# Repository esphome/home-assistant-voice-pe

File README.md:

# Nanobot Voice PE firmware

This repository is a focused fork of the official ESPHome source code for the
[Home Assistant Voice: Preview Edition](https://www.home-assistant.io/voice-pe/).
The upstream project remains available at
[`esphome/home-assistant-voice-pe`](https://github.com/esphome/home-assistant-voice-pe).

> [!IMPORTANT]
> Das aktuelle gekoppelte Pre-Release ist Firmware [`v1.4.2`](https://github.com/aschauera/home-assistant-voice-pe/releases/tag/v1.4.2) zusammen mit HA Voice Bridge [`v1.4.2`](https://github.com/aschauera/NanoBotSkills/releases/tag/v1.4.2). Beide verwenden dieselbe SemVer und denselben `v`-Tag. Bis zur gemeinsamen Hardwarevalidierung bleiben beide Pre-Releases; historische Releases wie Firmware `0.2.1` und Bridge `v1.4.1` bleiben unverändert.

## Offener Dialogmodus

Die Custom Firmware unterstützt einen begrenzten halbduplexen Dialog über die
bestehende Home-Assistant-Assist-Pipeline. Ein Wake Word öffnet die Session;
nach jeder Antwort wartet das Gerät ohne neues Wake Word auf den nächsten Turn.
`Stop`, definierte Exit-Phrasen, Mute, die mittlere Taste, Fehler, zehn Minuten
Gesamtlaufzeit oder zwanzig Antworten beenden sie. Während auf eine Frage
gewartet wird, beenden zwanzig Sekunden ohne Sprachbeginn die Session. Der
Leerlauf-Timeout startet nach jeder Antwort neu und wird mit dem ersten
Sprachbeginn angehalten.

Der LED-Ablauf bleibt über Dialogzustände hinweg ruhig: ein kurzer grüner Ring
öffnet die Session; Warten und Zuhören teilen denselben violett atmenden Ring;
Verarbeitung und ein Remote-ACK bleiben langsam amberfarben; die Antwort nutzt
denselben Amber-Ton mit schnellerem Puls. Nach jeder Antwort wird wieder violett
gewartet. Ein normales Ende zeigt genau einen kurzen orangefarbenen Impuls,
Fehler blinken weiterhin rot. Der Diagnosesensor `Dialog state` behält die
genauen textuellen Zustände für Bridge-Diagnosen bei.

Eine eingebettete lokale Ansage „Einen Moment.“ kann über die ESPHome-Aktion
`dialog_remote_ack` ausgelöst werden. Die Conversation-Agent-Integration muss
diesen Hook erst nach erfolglosem Local-Intent-Routing aufrufen; die Firmware
selbst kann lokal und remote nicht unterscheiden.

Architektur, Zustandsübergänge, LED-Prioritäten, Integrationsvertrag, Grenzen
und Rollback sind in [`docs/dialogmodus.md`](docs/dialogmodus.md) dokumentiert.
Barge-in und Full-Duplex sind ausdrücklich nicht Bestandteil dieser Version.

## Nanobot LED override

The firmware exposes a **Nanobot LED state** select entity to Home Assistant.
Selecting a state temporarily overrides the stock Assist animation:

| Option | Visual feedback | Automatic reset |
|---|---|---|
| `off` | Return control to the stock firmware | immediate |
| `thinking` | slow amber breathing ring | 90 seconds |
| `ack` | same slow amber breathing ring; no separate blue indication | 1.5 seconds |
| `replying` | faster amber breathing ring | 90 seconds |
| `follow_up` | violet breathing ring | 90 seconds |
| `done` | green confirmation | 1 second |
| `error` | red flash | 3 seconds |

Startup failure, provisioning, loss of the Home Assistant connection, hardware
interaction, ringing timers, mute, and native Voice Assistant error/not-ready
states retain priority over the Nanobot override. Every long-lived override has
a 90-second fail-safe and boot always starts with the override disabled.

Home Assistant can drive the state with `select.select_option`, for example:

```yaml
action: select.select_option
target:
  entity_id: select.home_assistant_voice_0a6c07_nanobot_led_state
data:
  option: ack
```

The exact entity ID is assigned by Home Assistant and may differ.

## Building and installing

The GitHub Actions **Build** workflow validates both firmware variants with
ESPHome 2026.10.0 and publishes build artifacts. The custom firmware intentionally disables the
official HTTP updater so an upstream release cannot silently overwrite it;
future updates are installed through ESPHome OTA or USB.

Do not flash an untested artifact onto the only production Voice PE. Download
the workflow artifact and use `home-assistant-voice-esp32s3.factory.bin` for the
initial USB installation. Keep the official web installer as the rollback path:

https://esphome.github.io/home-assistant-voice-pe/

### Vorkompiliertes Release per OTA installieren

Die vollständige agentenlesbare Anleitung mit Download, Prüfsummenprüfung,
Erreichbarkeitstest, Upload, Verifikation und Rollback steht unter
[`docs/ota-flashing.md`](docs/ota-flashing.md). Die verbindliche Zuordnung von
Firmware- und Bridge-Releases steht unter
[`docs/release-pairing.md`](docs/release-pairing.md).

Kurzablauf für das Standard-Voice-PE; `VOICE_PE_IP` durch die echte Adresse
ersetzen und das Produktionsgerät nur nach ausdrücklicher Freigabe flashen:

```bash
export FIRMWARE_RELEASE="v1.4.2"
export FIRMWARE_REPO="/home/nanobot/home-assistant-voice-pe"
export FIRMWARE_DIR="$HOME/Downloads/voice-pe-$FIRMWARE_RELEASE"
export VOICE_PE_IP="192.168.4.REPLACE_ME"

mkdir -p "$FIRMWARE_DIR"
cd "$FIRMWARE_DIR"
gh release download "$FIRMWARE_RELEASE" \
  --repo aschauera/home-assistant-voice-pe \
  --pattern "home-assistant-voice-$FIRMWARE_RELEASE.zip" \
  --pattern "SHA256SUMS.txt" \
  --clobber
grep "  home-assistant-voice-$FIRMWARE_RELEASE.zip$" SHA256SUMS.txt \
  | sha256sum -c -
unzip -o "home-assistant-voice-$FIRMWARE_RELEASE.zip"

python3 -m venv "$HOME/.venvs/esphome-2026.10.0"
source "$HOME/.venvs/esphome-2026.10.0/bin/activate"
python -m pip install "esphome==2026.10.0"

esphome upload "$FIRMWARE_REPO/home-assistant-voice.yaml" \
  --device "$VOICE_PE_IP" \
  --file "$FIRMWARE_DIR/home-assistant-voice-esp32s3.ota.bin" \
  --ota-platform esphome
```

Für OTA ausschließlich die Datei mit dem Suffix `.ota.bin` verwenden. Die
`.factory.bin` ist für USB-Installation oder Recovery bestimmt. Ein CLI-OTA
löscht die Gerätekonfiguration im ESPHome Device Builder nicht; ein späteres
`Install -> Wirelessly` aus dessen Weboberfläche kann die Custom Firmware aber
mit der dort gespeicherten YAML überschreiben.

For upstream setup and troubleshooting, see
https://voice-pe.home-assistant.io/.

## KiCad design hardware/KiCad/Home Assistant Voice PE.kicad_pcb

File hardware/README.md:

# Home Assistant Voice Preview Edition

This repo contains the KiCad project files for the Home Assistant Voice Preview Edition device.

It is licensed under the CERN-OHL-P v2.

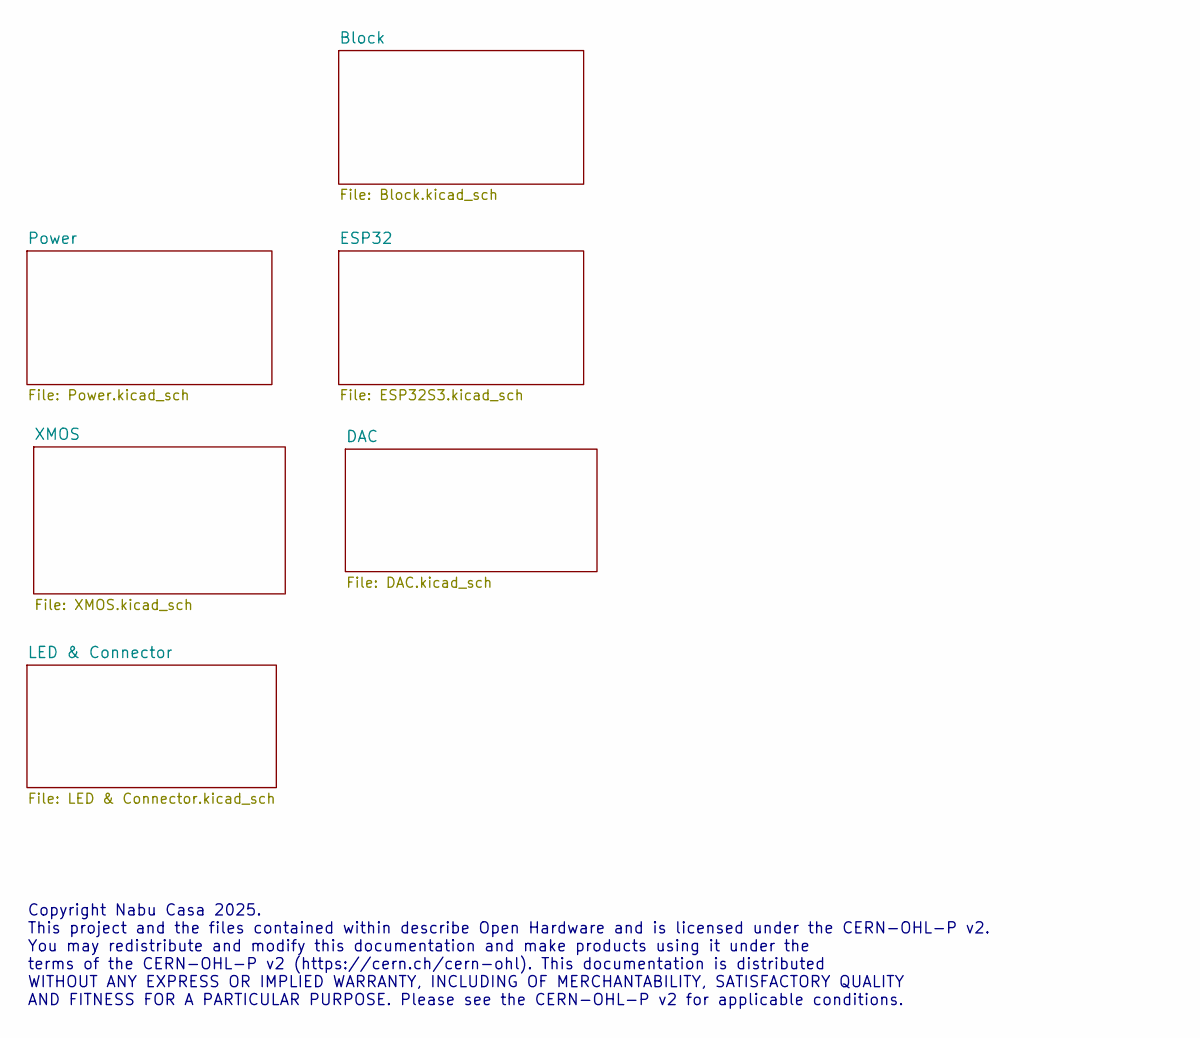
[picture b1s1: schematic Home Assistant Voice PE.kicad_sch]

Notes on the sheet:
Copyright Nabu Casa 2025. This project and the files contained within describe Open Hardware and is licensed under the CERN-OHL-P v2. You may redistribute and modify this documentation and make products using it under the terms of the CERN-OHL-P v2 (https://cern.ch/cern-ohl). This documentation is 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

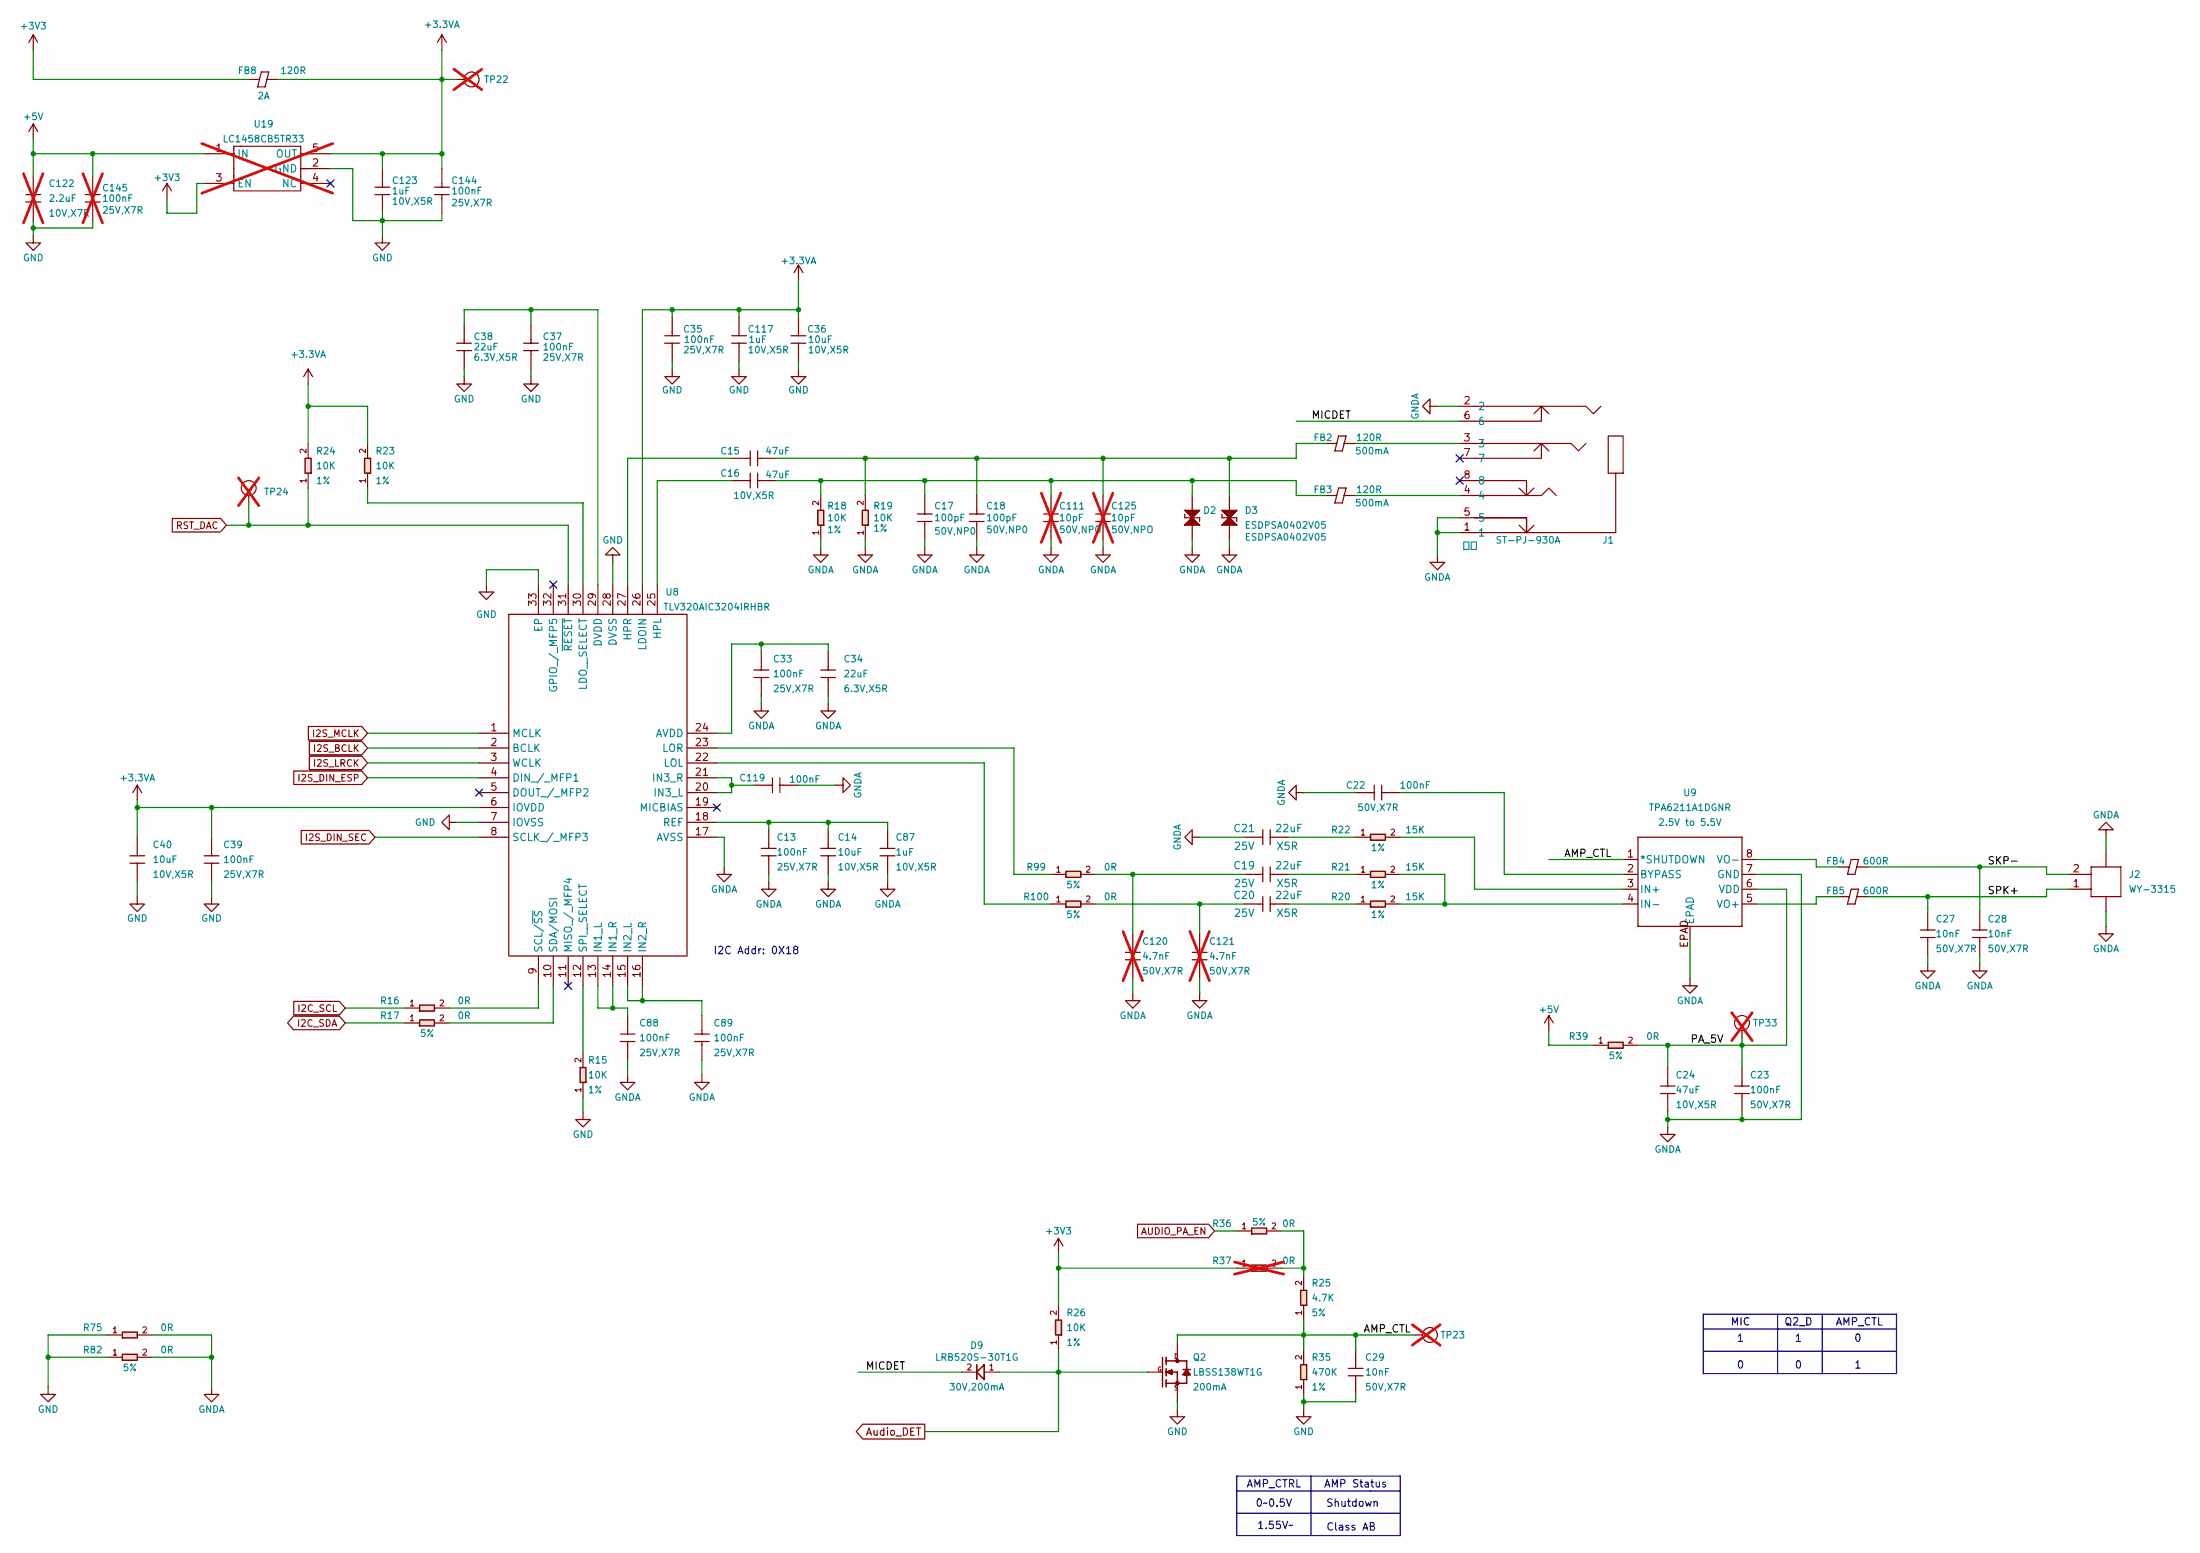
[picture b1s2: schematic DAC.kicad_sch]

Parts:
C13, C33, C35, C37, C39, C88, C89, C119, C144: 100nF; C0402; Voltage Rating 25V,X7R; MPN CC0402KRX7R8BB104
C14, C36, C40: 10uF; C0603; Voltage Rating 10V,X5R; MPN CL10A106KP8NNNC
C15, C16, C24: 47uF; C1206; Voltage Rating 10V,X5R; MPN CL31A476MPHNNNE
C17, C18: 100pF; C0402; Voltage Rating 50V,NP0; MPN CC0402FRNPO9BN101
C19, C20, C21: 22uF; C0805; Voltage Rating 25V; MPN CL21A226MAYNNNE
C22, C23: 100nF; C0603; Voltage Rating 50V,X7R; MPN CC0603KRX7R9BB104
C27, C28, C29: 10nF; C0402; Voltage Rating 50V,X7R; MPN CC0402KRX7R9BB103
C34, C38: 22uF; C0603; Voltage Rating 6.3V,X5R; MPN CL10A226MQ8NRNC
C87, C117, C123: 1uF; C0402; Voltage Rating 10V,X5R; MPN CL05A105KP5NNNC
C111, C125: 10pF; C0402; Voltage Rating 50V,NPO; MPN CC0402JRNPO9BN100; not fitted
C120, C121: 4.7nF; C0402; Voltage Rating 50V,X7R; MPN CC0402KRX7R9BB472; not fitted
C122: 2.2uF; C0603; Voltage Rating 10V,X7R; MPN CC0603KRX7R6BB225; not fitted
C145: 100nF; C0402; Voltage Rating 25V,X7R; MPN CC0402KRX7R8BB104; not fitted
D2, D3: ESDPSA0402V05; ESD-0402; MPN ESDPSA0402V05
D9: LRB520S-30T1G; SOD-523; Rating 30V,200mA; MPN LRB520S-30T1G
FB2, FB3: 120R; L0603; Rating 500mA; MPN BLM18AG121SN1D
FB4, FB5: 600R; L0603; Rating 500mA; MPN BLM18AG601SN1D
FB8: 120R; L0603; Rating 2A; MPN BLM18PG121SN1D
J1: ST-PJ-930A
J2: WY-3315; JST2P_1d25_7_55x4_25x4_8mm; MPN WY-3315
Q2: LBSS138WT1G; SOT-323; Rating 200mA; MPN LBSS138WT1G
R15, R18, R19, R23, R24, R26: 10K; R0402; Power Rating 1%; MPN RC0402FR-0710KL
R16, R17, R36: 0R; R0402; Power Rating 5%; MPN RC0402JR-070RL
R20, R21, R22: 15K; R0603; Power Rating 1%; MPN RC0603FR-0715KL
R25: 4.7K; R0402; Power Rating 5%; MPN RC0402JR-074K7L
R35: 470K; R0402; Power Rating 1%; MPN RC0402FR-07470KL
R37: 0R; R0402; Power Rating 5%; MPN RC0402JR-070RL; not fitted
R39, R99, R100: 0R; R0603; Power Rating 5%; MPN RC0603JR-070RL
R75, R82: 0R; R0805; Power Rating 5%; MPN RC0805JR-070RL
TP22, TP33: Test Point; TP-D45MIL; Part Type Test Point; not fitted
TP23, TP24: TEST-POINT; TP-D45MIL; not fitted
U8: TLV320AIC3204IRHBR; MPN TLV320AIC3204IRHBR; Mouser Part Number 595-V320AIC3204IRHBR
U9: TPA6211A1DGNR; DGN8_1d89X1P57; Rating 2.5V to 5.5V; MPN TI
U19: LC1458CB5TR33; SOT-23-5; MPN LC1458CB5TR33; not fitted

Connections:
+3.3VA: C35.1, C36.1, C39.1, C40.1, C117.1, C123.1, C144.1, FB8.2, R23.2, R24.2, TP22.1 (T), U8.6 (IOVDD), U8.26 (LDOIN), U19.5 (OUT)
+3V3: FB8.1, R26.2, R37.1, U19.3 (EN); also elsewhere on the board
+5V: C122.1, C145.1, R39.1, U19.1 (IN); also elsewhere on the board
/DAC/AMP_CTL: C29.1, Q2.3 (D), R25.1, R35.2, TP23.1 (T), U9.1 (*SHUTDOWN)
/DAC/MICDET: D9.2, J1.6
/DAC/PA_5V: C23.1, C24.1, R39.2, TP33.1 (T), U9.6 (VDD)
/DAC/SKP-: C28.1, FB4.2, J2.2
/DAC/SPK+: C27.1, FB5.2, J2.1
AUDIO_PA_EN: R36.1; also elsewhere on the board
Audio_DET: D9.1, Q2.1 (G), R26.1; also elsewhere on the board
GND: C29.2, C35.2, C36.2, C37.2, C38.2, C39.2, C40.2, C117.2, C122.2, C123.2, C144.2, C145.2, Q2.2 (S), R15.1, R35.1, R75.1, R82.1, U8.7 (IOVSS), U8.28 (DVSS), U8.33 (EP), U19.2 (GND); also elsewhere on the board
GNDA: C13.2, C14.2, C17.2, C18.2, C21.1, C22.1, C23.2, C24.2, C27.2, C28.2, C33.2, C34.2, C87.2, C88.2, C89.2, C111.2, C119.2, C120.2, C121.2, C125.2, D2.1, D3.1, J1.1, J1.2, J1.5, J2.3, J2.4, R18.1, R19.1, R75.2, R82.2, U8.17 (AVSS), U9.7 (GND), U9.EPAD
I2C_SCL: R16.1; also elsewhere on the board
I2C_SDA: R17.1; also elsewhere on the board
I2S_BCLK: U8.2 (BCLK); also elsewhere on the board
I2S_DIN_ESP: U8.4 (DIN_/_MFP1); also elsewhere on the board
I2S_DIN_SEC: U8.8 (SCLK_/_MFP3); also elsewhere on the board
I2S_LRCK: U8.3 (WCLK); also elsewhere on the board
I2S_MCLK: U8.1 (MCLK); also elsewhere on the board
unnamed: C19.2, R21.1
unnamed: C20.2, R20.1
unnamed: C21.2, R22.1
unnamed: C16.2, C17.1, C111.1, D2.2, FB3.1, R18.2
unnamed: C19.1, C120.1, R99.2
unnamed: C20.1, C121.1, R100.2
unnamed: C15.2, C18.1, C125.1, D3.2, FB2.1, R19.2
unnamed: FB2.2, J1.3
unnamed: FB3.2, J1.4
unnamed: R25.2, R36.2, R37.2
unnamed: C33.1, C34.1, U8.24 (AVDD)
unnamed: C37.1, C38.1, U8.29 (DVDD)
unnamed: C16.1, U8.25 (HPL)
unnamed: C15.1, U8.27 (HPR)
unnamed: C88.1, U8.13 (IN1_L), U8.14 (IN1_R)
unnamed: C89.1, U8.15 (IN2_L), U8.16 (IN2_R)
unnamed: C119.1, U8.20 (IN3_L), U8.21 (IN3_R)
unnamed: R23.1, U8.30 (LDO__SELECT)
unnamed: R100.1, U8.22 (LOL)
unnamed: R99.1, U8.23 (LOR)
unnamed: C13.1, C14.1, C87.1, U8.18 (REF)
unnamed: R16.2, U8.9 (SCL/~SS)
unnamed: R17.2, U8.10 (SDA/MOSI)
unnamed: R15.2, U8.12 (SPI__SELECT)
unnamed: C22.2, U9.2 (BYPASS)
unnamed: R22.2, U9.3 (IN+)
unnamed: R20.2, R21.2, U9.4 (IN-)
unnamed: FB5.1, U9.5 (VO+)
unnamed: FB4.1, U9.8 (VO-)
RST_DAC: R24.1, TP24.1 (T), U8.31 (~RESET); also elsewhere on the board

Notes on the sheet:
Shutdown
MIC
0~0.5V
Class AB
AMP_CTRL
AMP Status
AMP_CTL
1.55V~
Q2_D
I2C Addr: 0X18

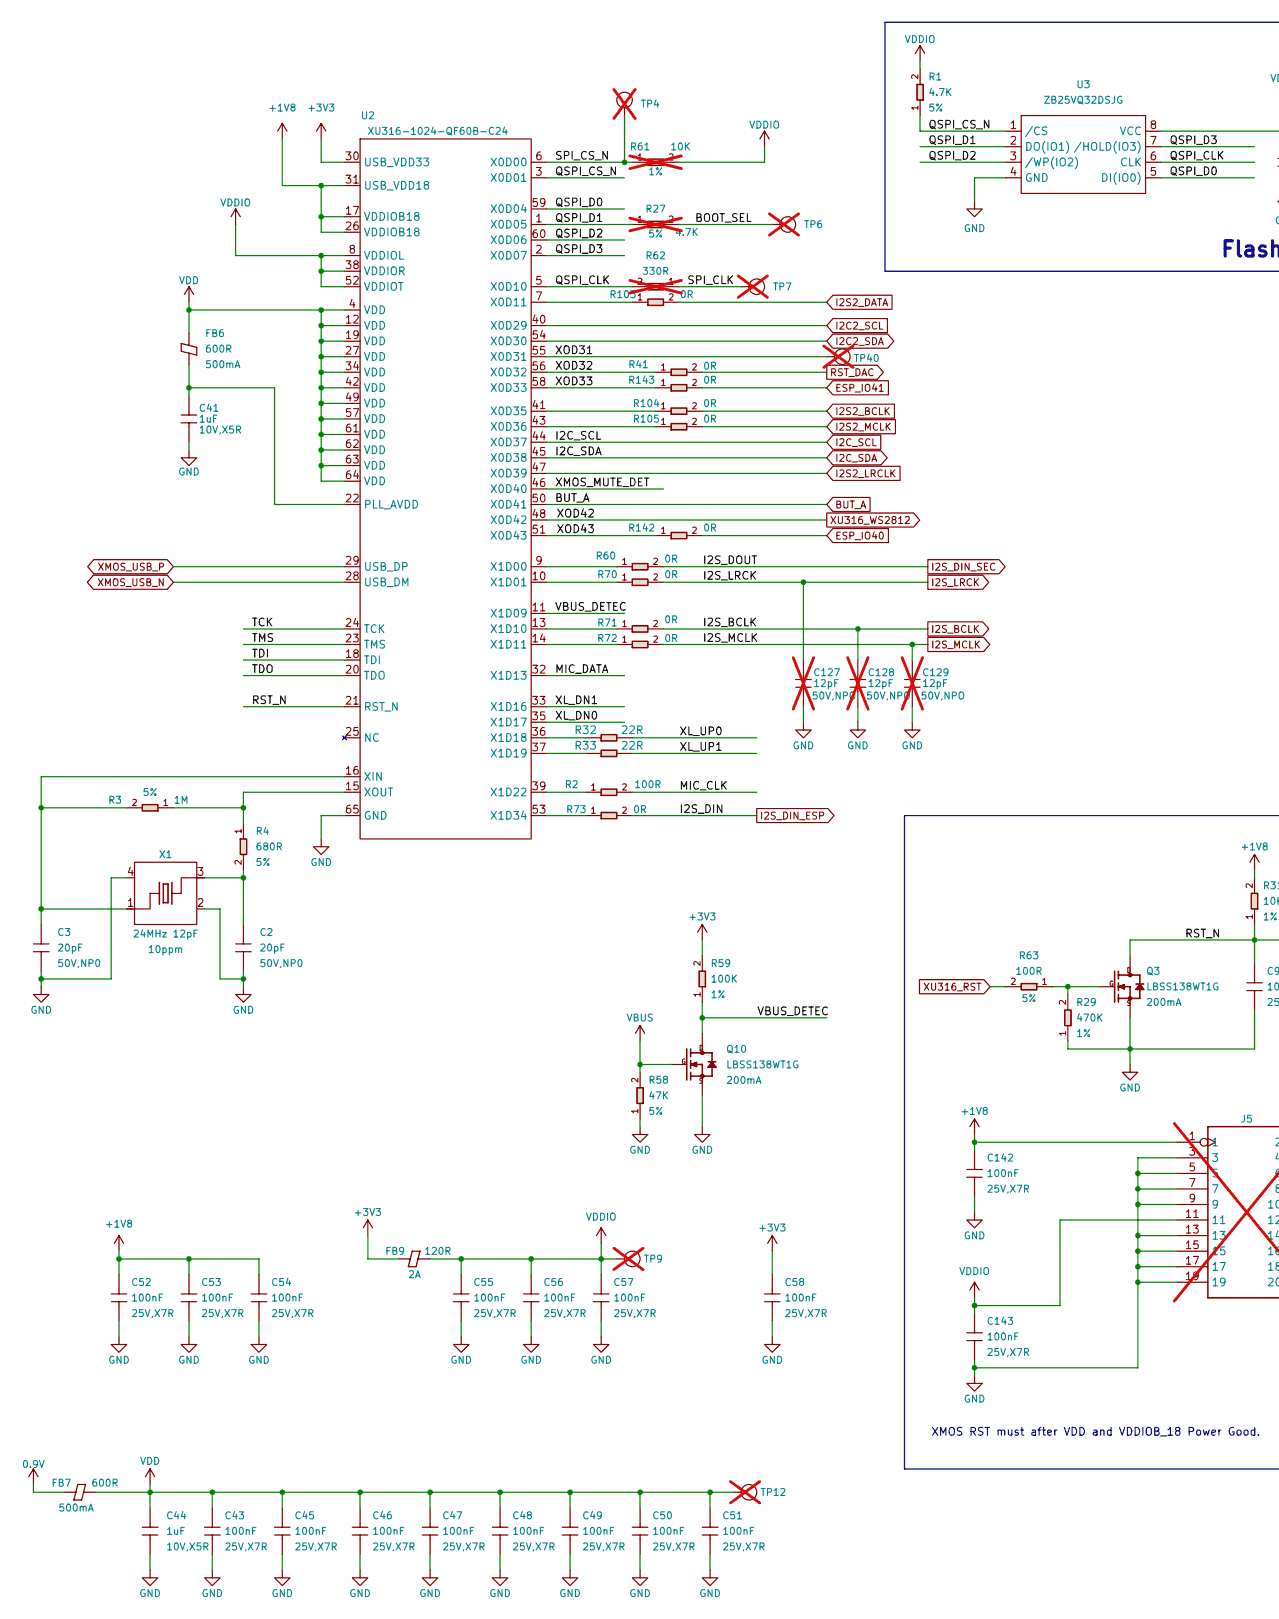
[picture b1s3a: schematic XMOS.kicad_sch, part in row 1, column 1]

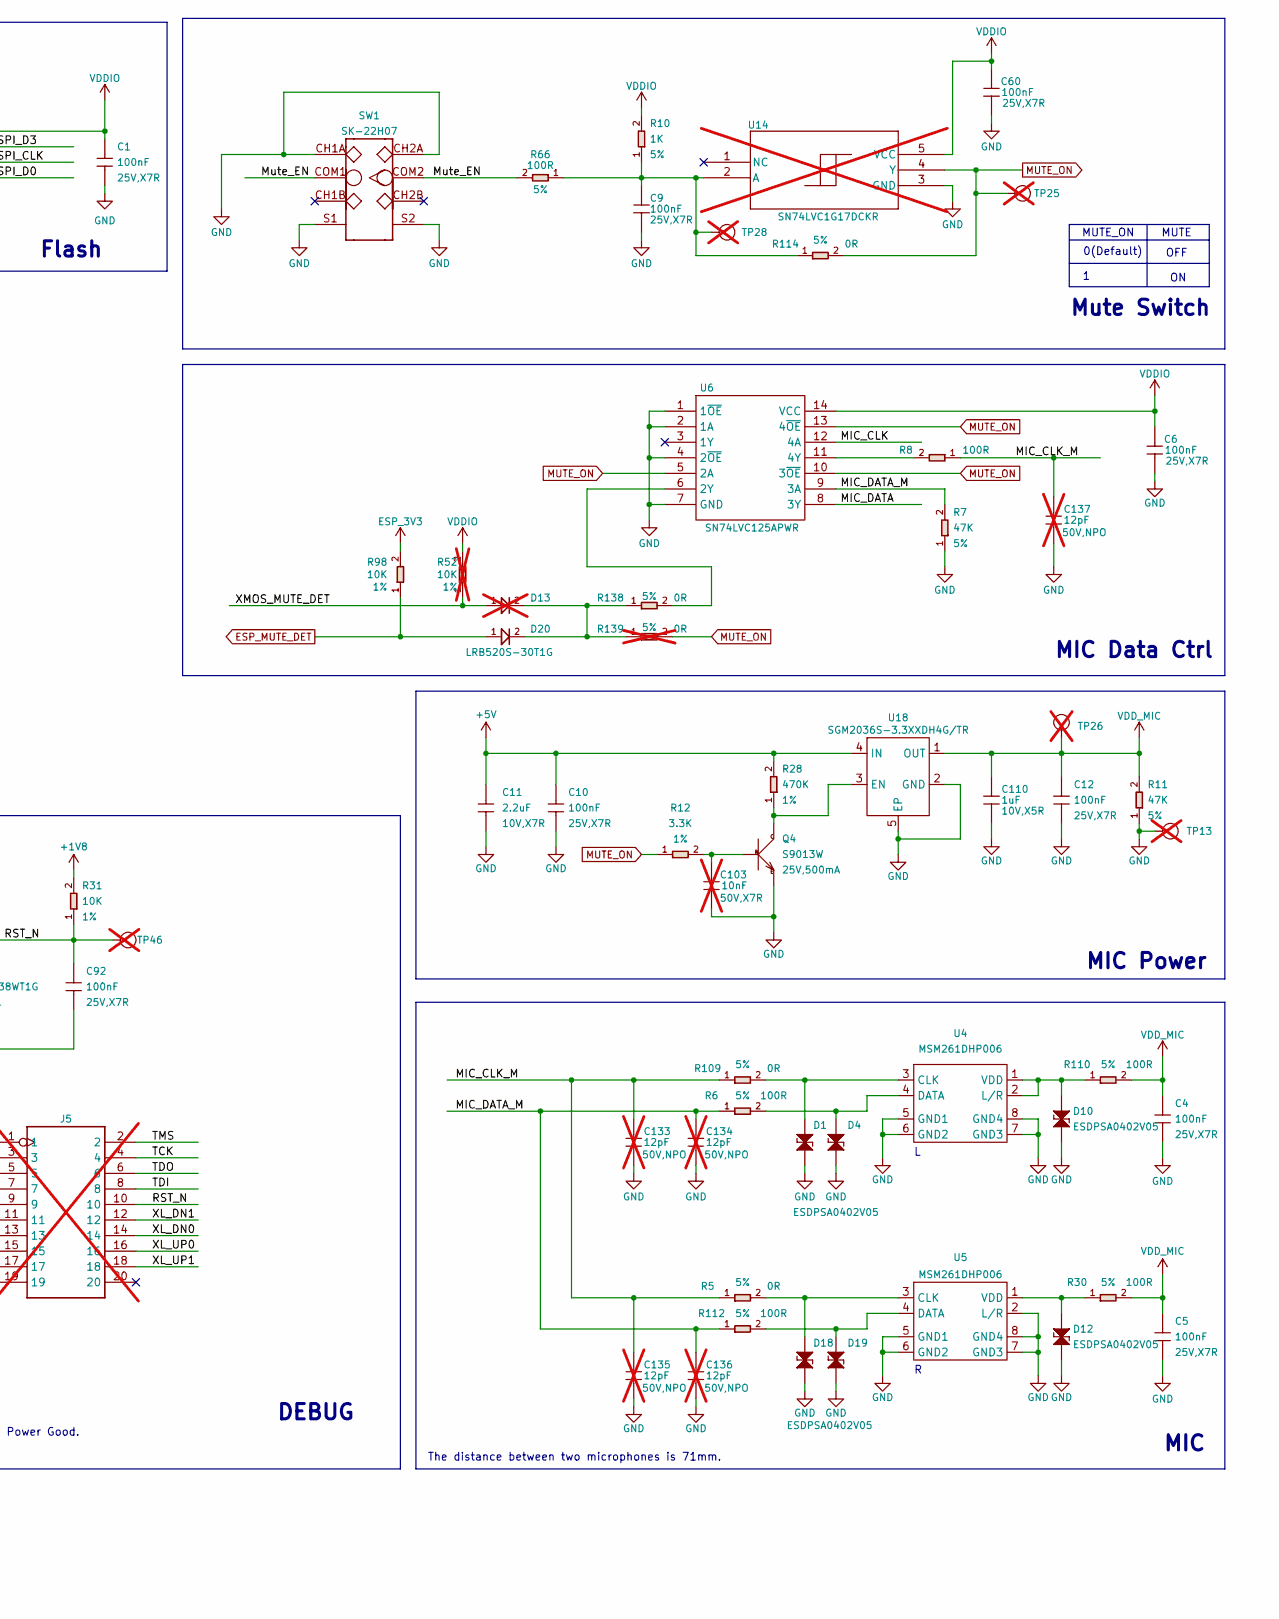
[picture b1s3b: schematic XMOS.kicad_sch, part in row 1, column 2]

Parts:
C1, C4, C5, C6, C9, C10, C12, C43, C45, C46, C47, C48, C49, C50, C51, C52, C53, C54, C55, C56, C57, C58, C60, C92, C142, C143: 100nF; C0402; Voltage Rating 25V,X7R; MPN CC0402KRX7R8BB104
C2, C3: 20pF; C0402; Voltage Rating 50V,NP0; MPN CC0402JRNPO9BN200
C11: 2.2uF; C0603; Voltage Rating 10V,X7R; MPN CC0603KRX7R6BB225
C41, C44, C110: 1uF; C0402; Voltage Rating 10V,X5R; MPN CL05A105KP5NNNC
C103: 10nF; C0402; Voltage Rating 50V,X7R; MPN CC0402KRX7R9BB103; not fitted
C127, C128, C129, C133, C134, C135, C136, C137: 12pF; C0402; Voltage Rating 50V,NPO; MPN CC0402JRNPO9BN120; not fitted
D1, D4, D10, D12, D18, D19: ESDPSA0402V05; ESD-0402; MPN ESDPSA0402V05
D13: LRB520S-30T1G; SOD-523; Rating 30V,200mA; MPN LRB520S-30T1G; not fitted
D20: LRB520S-30T1G; SOD-523; Rating 30V,200mA; MPN LRB520S-30T1G
FB6, FB7: 600R; L0603; Rating 500mA; MPN BLM18AG601SN1D
FB9: 120R; L0603; Rating 2A; MPN BLM18PG121SN1D
J5: JTAG_2X10_1.27_SMD; Part Type Header; not fitted
Q3, Q10: LBSS138WT1G; SOT-323; Rating 200mA; MPN LBSS138WT1G
Q4: S9013W; SOT-323; Rating 25V,500mA; MPN S9013W
R1: 4.7K; R0402; Power Rating 5%; MPN RC0402JR-074K7L
R2, R6, R8, R30, R63, R66, R110, R112: 100R; R0402; Power Rating 5%; MPN RC0402JR-07100RL
R3: 1M; R0402; Power Rating 5%; MPN RC0402JR-071ML
R4: 680R; R0402; Power Rating 5%; MPN RC0402JR-07680RL
R5, R41, R60, R70, R71, R72, R73, R103, R104, R105, R109, R114, R138, R142, R143: 0R; R0402; Power Rating 5%; MPN RC0402JR-070RL
R7, R11, R58: 47K; R0402; Power Rating 5%; MPN RC0402JR-0747KL
R10: 1K; R0402; Power Rating 5%; MPN RC0402JR-071KL
R12: 3.3K; R0402; Power Rating 1%; MPN RC0402JR-073K3L
R27: 4.7K; R0402; Power Rating 5%; MPN RC0402JR-074K7L; not fitted
R28, R29: 470K; R0402; Power Rating 1%; MPN RC0402FR-07470KL
R31, R98: 10K; R0402; Power Rating 1%; MPN RC0402FR-0710KL
R32, R33: 22R; R0402; Power Rating 5%; MPN RC0402JR-0722RL
R52, R61: 10K; R0402; Power Rating 1%; MPN RC0402FR-0710KL; not fitted
R59: 100K; R0402; Power Rating 1%; MPN RC0402FR-07100KL
R62: 330R; R0402; Power Rating 1%; MPN RC0402FR-07330RL; not fitted
R139: 0R; R0402; Power Rating 5%; MPN RC0402JR-070RL; not fitted
SW1: SK-22H07; SW6-2CH-12.7X7X4.7MM; MPN SK-22H07
TP4, TP6, TP7, TP9, TP12, TP13, TP25, TP26: TEST-POINT; TP-D45MIL; not fitted
TP28, TP40, TP46: Test Point; TP-D45MIL; Part Type Test Point; not fitted
U2: XU316-1024-QF60B-C24​; QFN_F60B-C24_XMO; MPN XU316-1024-QF60B-C24​
U3: ZB25VQ32DSJG; SOIC8-1.27-5.3X5.3MM; MPN ZB25VQ32DSJG
U4, U5: MSM261DHP006; MIC8P-0.85-4X3X1MM; MPN MIC-MSM261DHP006
U6: SN74LVC125APWR; MPN SN74LVC125APWR; Mouser Part Number 595-SN74LVC125APWR
U14: SN74LVC1G17DCKR; MPN SN74LVC1G17DCKR; not fitted
U18: SGM2036S-3.3XXDH4G/TR; X2SON4-0.625-1x1x0.6mm; Rating Vin MAX=6.5V; MPN SGM2036S-3.3XXDH4G/TR
X1: 24MHz 12pF; X4-SMD-2.0X1.6MM; Rating 10ppm; MPN Y2400FE001

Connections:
0.9V: FB7.1; also elsewhere on the board
+1V8: C52.1, C53.1, C54.1, C142.1, J5.1, R31.2, U2.17 (VDDIOB18), U2.26 (VDDIOB18), U2.31 (USB_VDD18); also elsewhere on the board
+3V3: C58.1, FB9.1, R59.2, U2.30 (USB_VDD33); also elsewhere on the board
+5V: C10.1, C11.1, R28.2, U18.4 (IN); also elsewhere on the board
/XMOS/BOOT_SEL: R27.2, TP6.1 (T)
/XMOS/MIC_CLK: R2.2, U6.12 (4A)
/XMOS/MIC_CLK_M: C133.1, C135.1, C137.1, R5.1, R8.1, R109.1
/XMOS/MIC_DATA: U2.32 (X1D13), U6.8 (3Y)
/XMOS/MIC_DATA_M: C134.1, C136.1, R6.1, R7.2, R112.1, U6.9 (3A)
/XMOS/Mute_EN: R66.2, SW1.COM1, SW1.COM2
/XMOS/QSPI_CLK: R62.2, U2.5 (X0D10), U3.6 (CLK)
/XMOS/QSPI_CS_N: R1.1, U2.3 (X0D01), U3.1 (/CS)
/XMOS/QSPI_D0: U2.59 (X0D04), U3.5 (DI(IO0))
/XMOS/QSPI_D1: R27.1, U2.1 (X0D05), U3.2 (DO(IO1))
/XMOS/QSPI_D2: U2.60 (X0D06), U3.3 (/WP(IO2))
/XMOS/QSPI_D3: U2.2 (X0D07), U3.7 (/HOLD(IO3))
/XMOS/RST_N: C92.1, J5.10, Q3.3 (D), R31.1, TP46.1 (T), U2.21 (RST_N)
/XMOS/SPI_CLK: R62.1, TP7.1 (T)
/XMOS/SPI_CS_N: R61.1, TP4.1 (T), U2.6 (X0D00)
/XMOS/TCK: J5.4, U2.24 (TCK)
/XMOS/TDI: J5.8, U2.18 (TDI)
/XMOS/TDO: J5.6, U2.20 (TDO)
/XMOS/TMS: J5.2, U2.23 (TMS)
/XMOS/VBUS_DETEC: Q10.3 (D), R59.1, U2.11 (X1D09)
/XMOS/XL_DN0: J5.14, U2.35 (X1D17)
/XMOS/XL_DN1: J5.12, U2.33 (X1D16)
/XMOS/XL_UP0: J5.16, R32.2
/XMOS/XL_UP1: J5.18, R33.2
/XMOS/XMOS_MUTE_DET: D13.1, R52.1, U2.46 (X0D40)
/XMOS/XOD31: TP40.1 (T), U2.55 (X0D31)
/XMOS/XOD32: R41.1, U2.56 (X0D32)
/XMOS/XOD33: R143.1, U2.58 (X0D33)
/XMOS/XOD43: R142.1, U2.51 (X0D43)
BUT_A: U2.50 (X0D41); also elsewhere on the board
ESP_3V3: R98.2; also elsewhere on the board
ESP_IO40: R142.2; also elsewhere on the board
ESP_IO41: R143.2; also elsewhere on the board
ESP_MUTE_DET: D20.1, R98.1; also elsewhere on the board
GND: C1.2, C2.2, C3.2, C4.2, C5.2, C6.2, C9.2, C10.2, C11.2, C12.2, C41.2, C43.2, C44.2, C45.2, C46.2, C47.2, C48.2, C49.2, C50.2, C51.2, C52.2, C53.2, C54.2, C55.2, C56.2, C57.2, C58.2, C60.2, C92.2, C103.2, C110.2, C127.2, C128.2, C129.2, C133.2, C134.2, C135.2, C136.2, C137.2, C142.2, C143.2, D1.1, D4.1, D10.1, D12.1, D18.1, D19.1, J5.3, J5.5, J5.7, J5.9, J5.13, J5.15, J5.17, J5.19, Q3.2 (S), Q4.2 (E), Q10.2 (S), R7.1, R11.1, R29.1, R58.1, SW1.CH1A, SW1.CH2A, SW1.S1, SW1.S2, TP13.1 (T), U2.65 (GND), U3.4 (GND), U4.5 (GND1), U4.6 (GND2), U4.7 (GND3), U4.8 (GND4), U5.2 (L/R), U5.5 (GND1), U5.6 (GND2), U5.7 (GND3), U5.8 (GND4), U6.1 (1~OE), U6.2 (1A), U6.4 (2~OE), U6.7 (GND), U14.3 (GND), U18.2 (GND), U18.5 (EP), X1.2, X1.4; also elsewhere on the board
I2C2_SCL: U2.40 (X0D29); also elsewhere on the board
I2C2_SDA: U2.54 (X0D30); also elsewhere on the board
I2C_SCL: U2.44 (X0D37); also elsewhere on the board
I2C_SDA: U2.45 (X0D38); also elsewhere on the board
I2S2_BCLK: R104.2; also elsewhere on the board
I2S2_DATA: R103.2; also elsewhere on the board
I2S2_LRCLK: U2.47 (X0D39); also elsewhere on the board
I2S2_MCLK: R105.2; also elsewhere on the board
I2S_BCLK: C128.1, R71.2; also elsewhere on the board
I2S_DIN_ESP: R73.2; also elsewhere on the board
I2S_DIN_SEC: R60.2; also elsewhere on the board
I2S_LRCK: C127.1, R70.2; also elsewhere on the board
I2S_MCLK: C129.1, R72.2; also elsewhere on the board
MUTE_ON: R12.1, R114.2, R139.2, TP25.1 (T), U6.5 (2A), U6.10 (3~OE), U6.13 (4~OE), U14.4 (Y)
unnamed: C2.1, R4.2, X1.3
unnamed: D13.2, D20.2, R138.1, R139.1
unnamed: Q3.1 (G), R29.2, R63.1
unnamed: C103.1, Q4.1 (B), R12.2
unnamed: Q4.3 (C), R28.1, U18.3 (EN)
unnamed: C9.1, R10.1, R66.1, R114.1, TP28.1 (T), U14.2 (A)
unnamed: C41.1, FB6.1, U2.22 (PLL_AVDD)
unnamed: R103.1, U2.7 (X0D11)
unnamed: R104.1, U2.41 (X0D35)
unnamed: R105.1, U2.43 (X0D36)
unnamed: R60.1, U2.9 (X1D00)
unnamed: R70.1, U2.10 (X1D01)
unnamed: R71.1, U2.13 (X1D10)
unnamed: R72.1, U2.14 (X1D11)
unnamed: R32.1, U2.36 (X1D18)
unnamed: R33.1, U2.37 (X1D19)
unnamed: R2.1, U2.39 (X1D22)
unnamed: R73.1, U2.53 (X1D34)
unnamed: C3.1, R3.2, U2.16 (XIN), X1.1
unnamed: R3.1, R4.1, U2.15 (XOUT)
unnamed: D1.2, R109.2, U4.3 (CLK)
unnamed: D4.2, R6.2, U4.4 (DATA)
unnamed: D10.2, R110.1, U4.1 (VDD), U4.2 (L/R)
unnamed: D18.2, R5.2, U5.3 (CLK)
unnamed: D19.2, R112.2, U5.4 (DATA)
unnamed: D12.2, R30.1, U5.1 (VDD)
unnamed: R138.2, U6.6 (2Y)
unnamed: R8.2, U6.11 (4Y)
RST_DAC: R41.2; also elsewhere on the board
VBUS: Q10.1 (G), R58.2; also elsewhere on the board
VDD: C43.1, C44.1, C45.1, C46.1, C47.1, C48.1, C49.1, C50.1, C51.1, FB6.2, FB7.2, TP12.1 (T), U2.4 (VDD), U2.12 (VDD), U2.19 (VDD), U2.27 (VDD), U2.34 (VDD), U2.42 (VDD), U2.49 (VDD), U2.57 (VDD), U2.61 (VDD), U2.62 (VDD), U2.63 (VDD), U2.64 (VDD)
VDDIO: C1.1, C6.1, C55.1, C56.1, C57.1, C60.1, C143.1, FB9.2, J5.11, R1.2, R10.2, R52.2, R61.2, TP9.1 (T), U2.8 (VDDIOL), U2.38 (VDDIOR), U2.52 (VDDIOT), U3.8 (VCC), U6.14 (VCC), U14.5 (VCC)
VDD_MIC: C4.1, C5.1, C12.1, C110.1, R11.2, R30.2, R110.2, TP26.1 (T), U18.1 (OUT)
XMOS_USB_N: U2.28 (USB_DM); also elsewhere on the board
XMOS_USB_P: U2.29 (USB_DP); also elsewhere on the board
XU316_RST: R63.2; also elsewhere on the board
XU316_WS2812: U2.48 (X0D42); also elsewhere on the board

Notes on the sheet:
MUTE_ON
The distance between two microphones is 71mm.
DEBUG
Flash
Mute Switch
MIC Data Ctrl
OFF
MIC
MUTE
XMOS RST must after VDD and VDDIOB_18 Power Good.
0(Default)
MIC Power

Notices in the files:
hardware/KiCad/DAC.kicad_sch:
Licensed under CERN-OHL-P v2
hardware/KiCad/Home Assistant Voice PE.kicad_sch:
terms of the CERN-OHL-P v2 (https://cern.ch/cern-ohl). This documentation is distributed
